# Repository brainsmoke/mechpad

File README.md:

# mechanical keypad

|  |
|-|
|  |

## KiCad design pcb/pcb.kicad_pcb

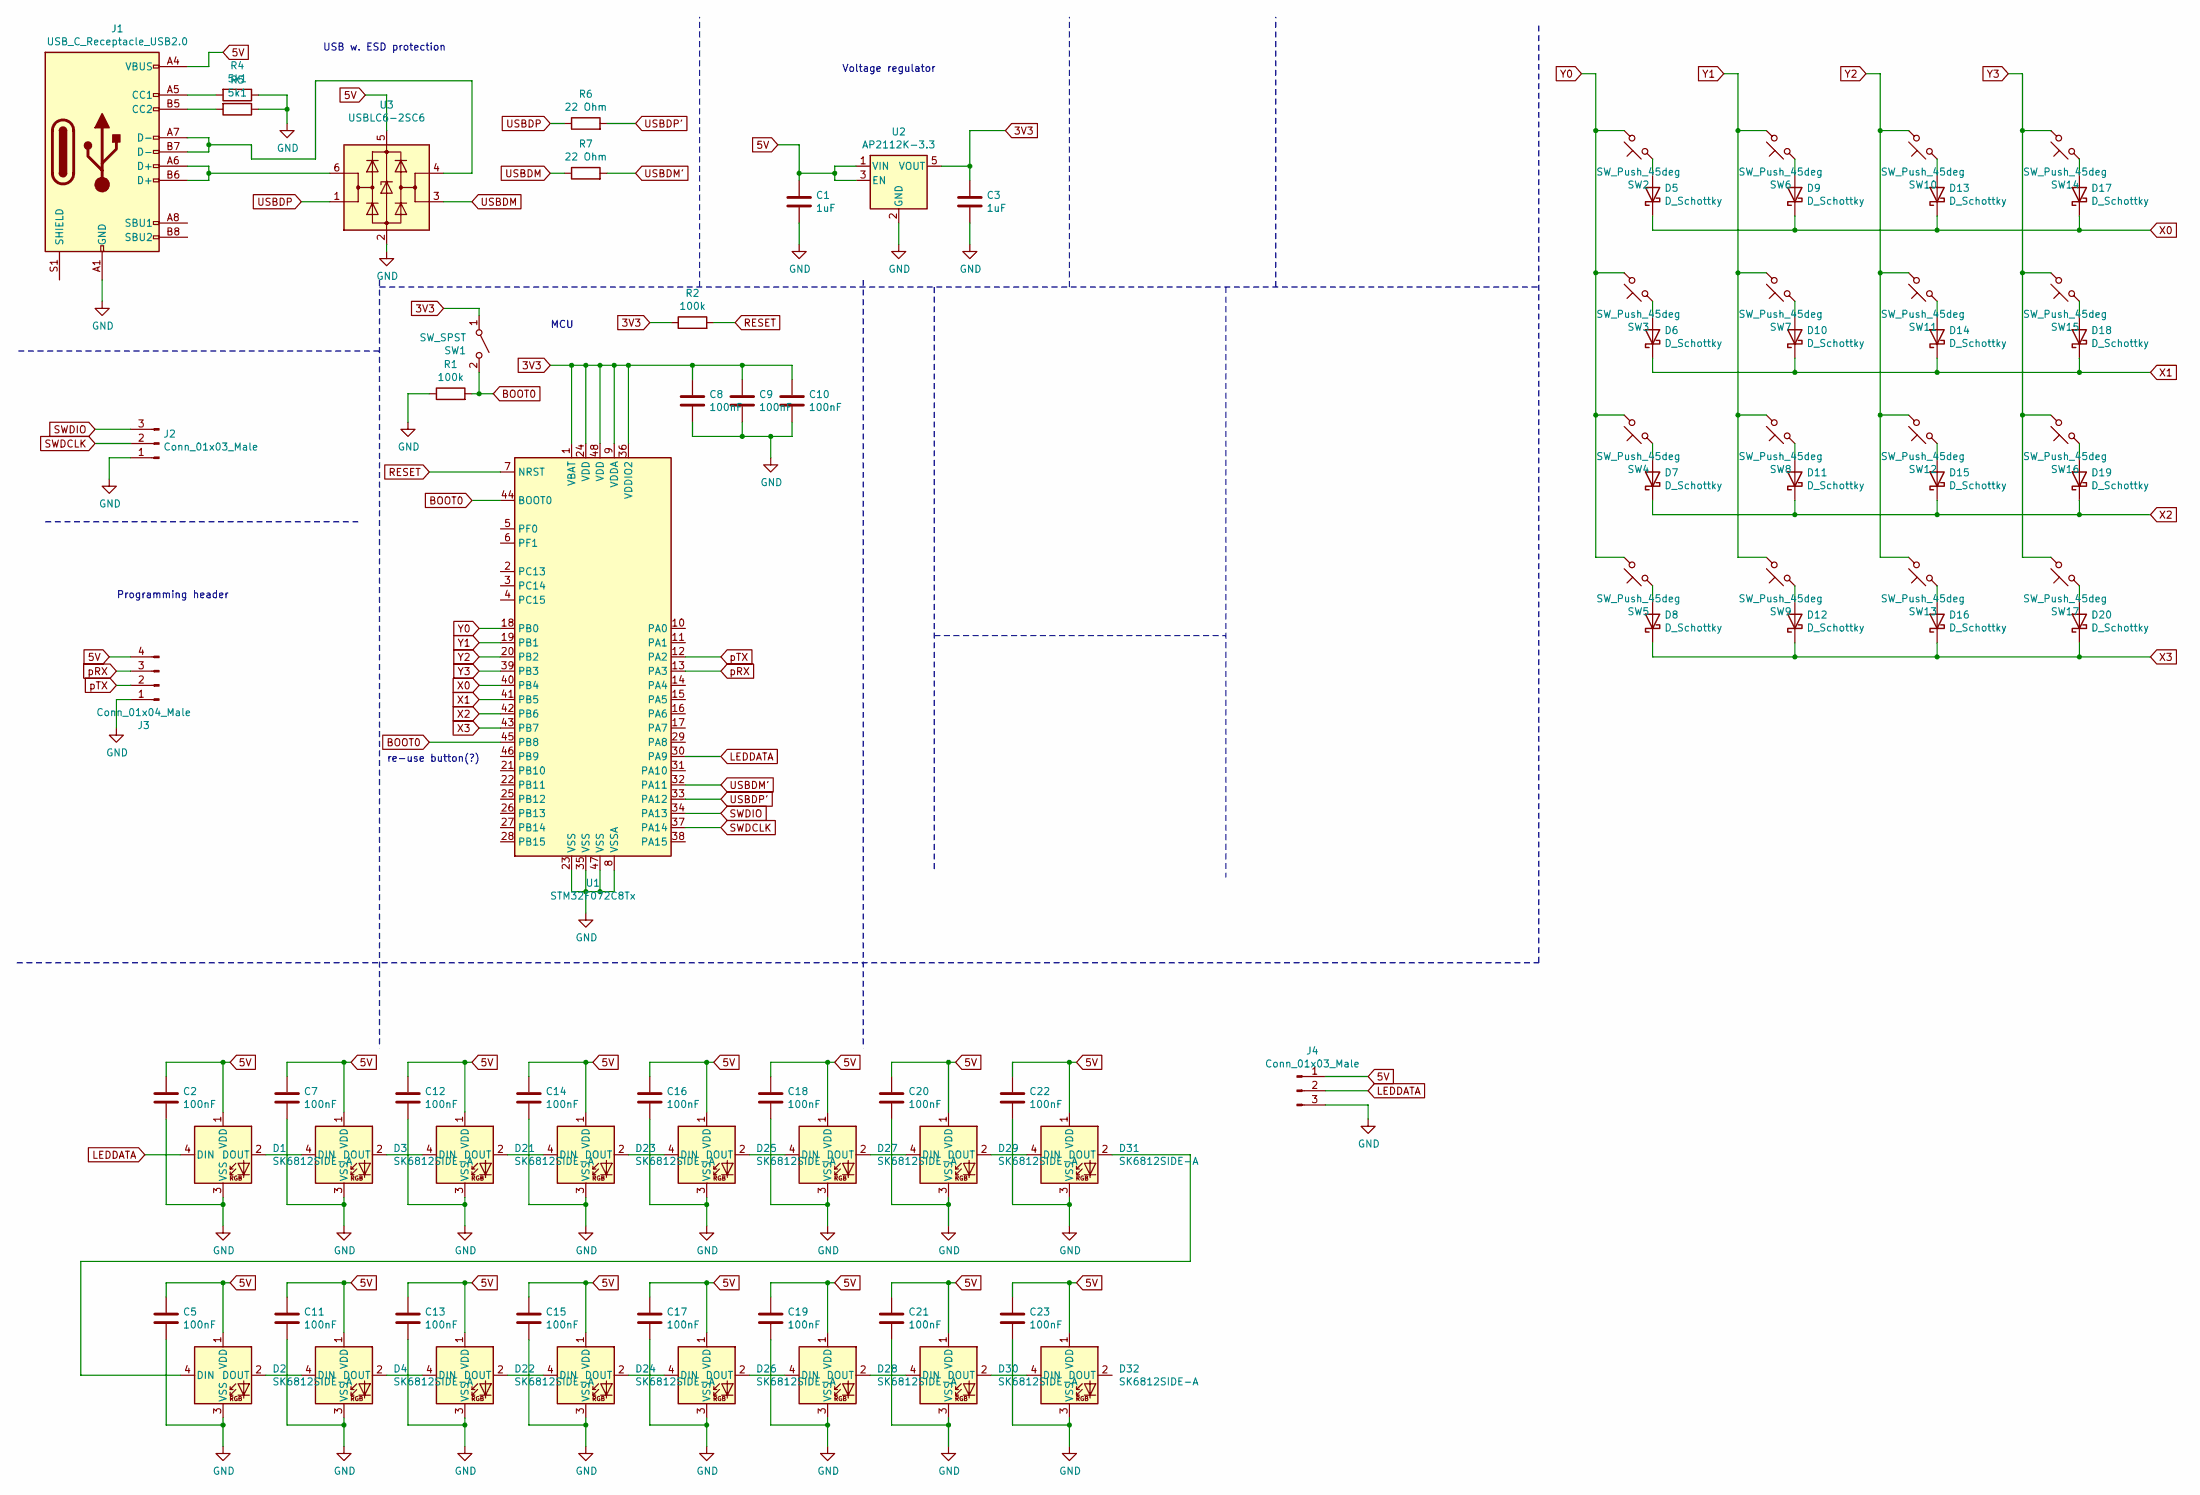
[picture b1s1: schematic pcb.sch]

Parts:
C1, C3: 1uF; C_0603_1608Metric
C2, C5, C7, C8, C9, C10, C11, C12, C13, C14, C15, C16, C17, C18, C19, C20, C21, C22, C23: 100nF; C_0603_1608Metric; LCSC C14663
D1, D2, D3, D4, D21, D22, D23, D24, D25, D26, D27, D28, D29, D30, D31, D32: SK6812SIDE-A; LED_SK6812SIDE-A_4020_pinlayout_asif50505-padssecure; LCSC C2890037
D5, D6, D7, D8, D9, D10, D11, D12, D13, D14, D15, D16, D17, D18, D19, D20: D_Schottky; D_SOD-123
J1: USB_C_Receptacle_USB2.0; USB_C_Receptacle_HRO_TYPE-C-31-M-12
J2, J4: Conn_01x03_Male; PinHeader_1x03_P2.54mm_Vertical
J3: Conn_01x04_Male; PinHeader_1x04_P2.54mm_Vertical
R1, R2: 100k; R_0603_1608Metric
R4, R5: 5k1; R_0603_1608Metric
R6, R7: 22 Ohm; R_0603_1608Metric
SW1: SW_SPST; SW_Push_1P1T_NO_CK_KMR2
SW2, SW3, SW4, SW5, SW6, SW7, SW8, SW9, SW10, SW11, SW12, SW13, SW14, SW15, SW16, SW17: SW_Push_45deg; SW_Cherry_MX_1.00u_PCB
U1: STM32F072C8Tx; LQFP-48_7x7mm_P0.5mm
U2: AP2112K-3.3; SOT-23-5
U3: USBLC6-2SC6; SOT-23-6

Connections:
3V3: C3.1, C8.1, C9.1, C10.1, R2.1, SW1.1 (A), U1.1 (VBAT), U1.9 (VDDA), U1.24 (VDD), U1.36 (VDDIO2), U1.48 (VDD), U2.5 (VOUT)
5V: C1.1, C2.1, C5.1, C7.1, C11.1, C12.1, C13.1, C14.1, C15.1, C16.1, C17.1, C18.1, C19.1, C20.1, C21.1, C22.1, C23.1, D1.1 (VDD), D2.1 (VDD), D3.1 (VDD), D4.1 (VDD), D21.1 (VDD), D22.1 (VDD), D23.1 (VDD), D24.1 (VDD), D25.1 (VDD), D26.1 (VDD), D27.1 (VDD), D28.1 (VDD), D29.1 (VDD), D30.1 (VDD), D31.1 (VDD), D32.1 (VDD), J1.A4 (VBUS), J1.A9 (VBUS), J1.B4 (VBUS), J1.B9 (VBUS), J3.4, J4.1, U2.1 (VIN), U2.3 (EN), U3.5 (VBUS)
BOOT0: R1.2, SW1.2 (B), U1.44 (BOOT0), U1.45 (PB8)
GND: C1.2, C2.2, C3.2, C5.2, C7.2, C8.2, C9.2, C10.2, C11.2, C12.2, C13.2, C14.2, C15.2, C16.2, C17.2, C18.2, C19.2, C20.2, C21.2, C22.2, C23.2, D1.3 (VSS), D2.3 (VSS), D3.3 (VSS), D4.3 (VSS), D21.3 (VSS), D22.3 (VSS), D23.3 (VSS), D24.3 (VSS), D25.3 (VSS), D26.3 (VSS), D27.3 (VSS), D28.3 (VSS), D29.3 (VSS), D30.3 (VSS), D31.3 (VSS), D32.3 (VSS), J1.A1 (GND), J1.A12 (GND), J1.B1 (GND), J1.B12 (GND), J2.1, J3.1, J4.3, R1.1, R4.1, R5.1, U1.8 (VSSA), U1.23 (VSS), U1.35 (VSS), U1.47 (VSS), U2.2 (GND), U3.2 (GND)
LEDDATA: D1.4 (DIN), J4.2, U1.30 (PA9)
unnamed: D1.2 (DOUT), D3.4 (DIN)
unnamed: D2.2 (DOUT), D4.4 (DIN)
unnamed: D2.4 (DIN), D31.2 (DOUT)
unnamed: D5.2 (A), SW2.1
unnamed: D6.2 (A), SW3.1
unnamed: D7.2 (A), SW4.1
unnamed: D8.2 (A), SW5.1
unnamed: D9.2 (A), SW6.1
unnamed: D10.2 (A), SW7.1
unnamed: D11.2 (A), SW8.1
unnamed: D12.2 (A), SW9.1
unnamed: D13.2 (A), SW10.1
unnamed: D14.2 (A), SW11.1
unnamed: D15.2 (A), SW12.1
unnamed: D16.2 (A), SW13.1
unnamed: D17.2 (A), SW14.1
unnamed: D18.2 (A), SW15.1
unnamed: D19.2 (A), SW16.1
unnamed: D20.2 (A), SW17.1
unnamed: D21.2 (DOUT), D23.4 (DIN)
unnamed: D3.2 (DOUT), D21.4 (DIN)
unnamed: D22.2 (DOUT), D24.4 (DIN)
unnamed: D4.2 (DOUT), D22.4 (DIN)
unnamed: D23.2 (DOUT), D25.4 (DIN)
unnamed: D24.2 (DOUT), D26.4 (DIN)
unnamed: D25.2 (DOUT), D27.4 (DIN)
unnamed: D26.2 (DOUT), D28.4 (DIN)
unnamed: D27.2 (DOUT), D29.4 (DIN)
unnamed: D28.2 (DOUT), D30.4 (DIN)
unnamed: D29.2 (DOUT), D31.4 (DIN)
unnamed: D30.2 (DOUT), D32.4 (DIN)
unnamed: J1.A5 (CC1), R4.2
unnamed: J1.A6 (D+), J1.B6 (D+), U3.6 (I/O1)
unnamed: J1.A7 (D-), J1.B7 (D-), U3.4 (I/O2)
unnamed: J1.B5 (CC2), R5.2
RESET: R2.2, U1.7 (NRST)
SWDCLK: J2.2, U1.37 (PA14)
SWDIO: J2.3, U1.34 (PA13)
USBDM: R7.1, U3.3 (I/O2)
USBDM': R7.2, U1.32 (PA11)
USBDP: R6.1, U3.1 (I/O1)
USBDP': R6.2, U1.33 (PA12)
X0: D5.1 (K), D9.1 (K), D13.1 (K), D17.1 (K), U1.40 (PB4)
X1: D6.1 (K), D10.1 (K), D14.1 (K), D18.1 (K), U1.41 (PB5)
X2: D7.1 (K), D11.1 (K), D15.1 (K), D19.1 (K), U1.42 (PB6)
X3: D8.1 (K), D12.1 (K), D16.1 (K), D20.1 (K), U1.43 (PB7)
Y0: SW2.2, SW3.2, SW4.2, SW5.2, U1.18 (PB0)
Y1: SW6.2, SW7.2, SW8.2, SW9.2, U1.19 (PB1)
Y2: SW10.2, SW11.2, SW12.2, SW13.2, U1.20 (PB2)
Y3: SW14.2, SW15.2, SW16.2, SW17.2, U1.39 (PB3)
pRX: J3.3, U1.13 (PA3)
pTX: J3.2, U1.12 (PA2)

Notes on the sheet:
Programming header
USB w. ESD protection
Voltage regulator
MCU
re-use button(?)

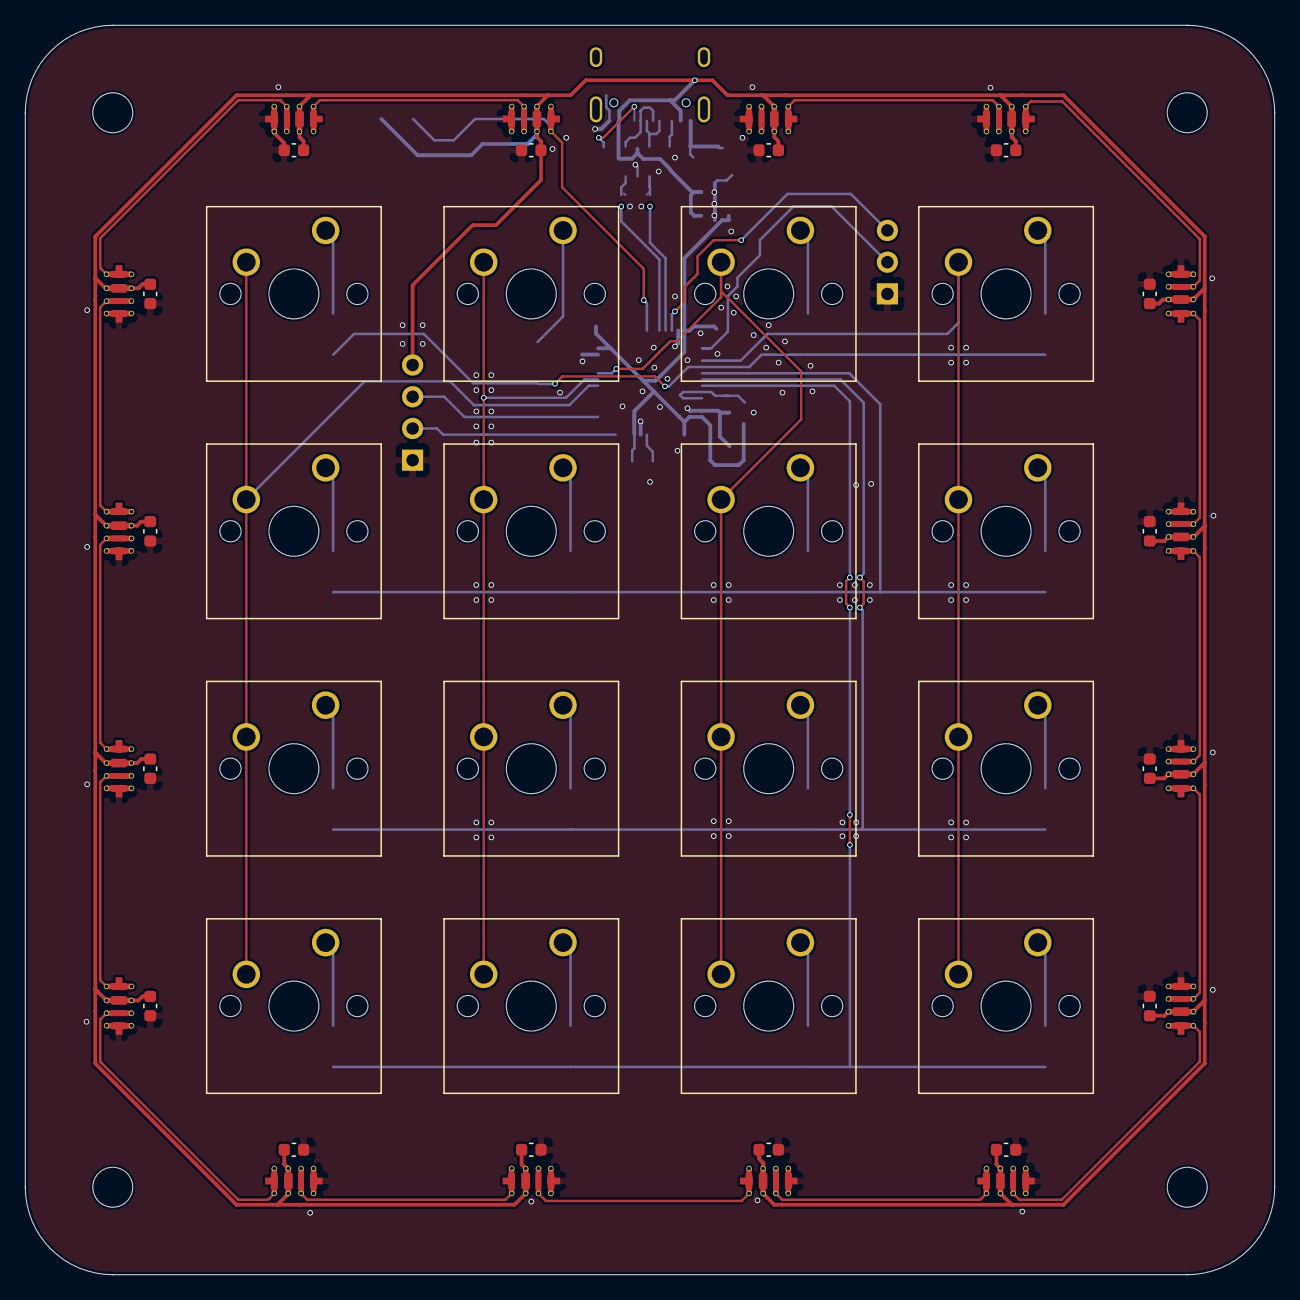
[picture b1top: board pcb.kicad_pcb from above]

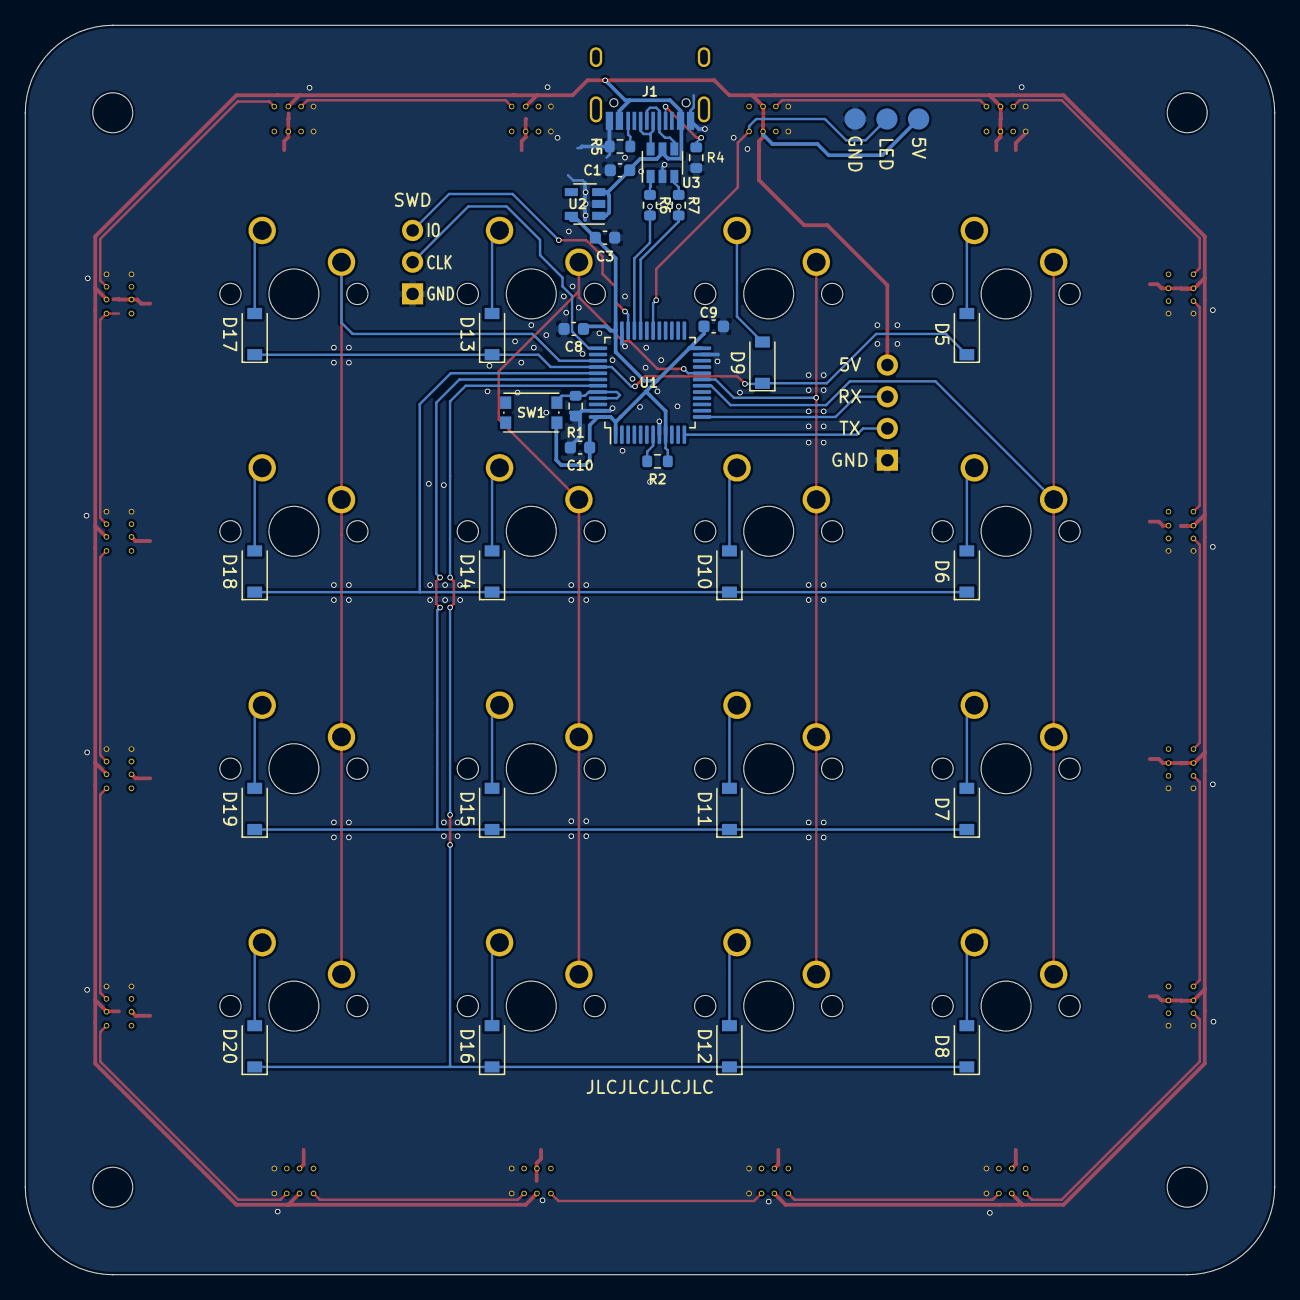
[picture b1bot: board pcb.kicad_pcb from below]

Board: 2 copper layers, 100.0 x 100.0 mm, 83 parts (34 on the bottom side), 57 nets.

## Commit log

2023-10-17 init commit
2023-10-17 change headers
2023-10-17 add gerbers
2023-10-17 move pcb to subdir
2023-10-20 add keycap files
2023-10-21 rename dir
2023-10-21 add empty glyph
2023-10-21 clean up construction in flat_keys.scad
2023-10-21 add stl files
2023-11-01 correct silkscreen labels (oops)
2023-11-02 make leds work
2023-11-03 mak keys work
2023-11-03 move led code to common dir
2023-11-03 add some more led animations
2023-11-03 add boot0 button
2023-11-03 remove osc.
2023-11-03 compensate for weak red
2023-11-03 factor out keypad code
2023-11-04 stm32f103 -> stm32f072
2023-11-04 remove obsolete comment
2023-11-04 add ELF to DeFUse tool
2023-11-04 the big endian in the spec is a lie (at least in dfu-util
2023-11-11 make leds brighter
2023-11-11 add images
2023-11-12 add case
2023-11-18 add USB HID keypad example
2023-11-18 add link to HID key definitions document
2023-11-18 fix name of consumer page
2023-11-18 change key bindings
2023-11-19 improve animation
2023-11-19 remove ferrite
2023-11-19 wait for descriptor read before sending packets
2023-11-19 use common code for animations
2023-11-19 add led probe pads
2023-11-21 make solder pads more solid in case of desoldering
2023-11-22 optimize tracks
2023-11-23 speed up animation
2023-11-24 add usb serial example
2023-11-24 mpd frontend
2023-11-27 ws2812b-4020 -> sk6812-side-a
2023-11-28 don't block when the OS isn't listening
2023-11-28 increase clearance
2023-11-28 add comment with possible tweaks
2023-12-15 add case for v2
2023-12-15 add gerbers for v2
2023-12-17 remove unecessary pull-up on USB-DP
2024-04-10 case for v2 improvements
2024-06-29 add key STLs optimised for fdm
2024-07-05 use Makefile for keys
2024-07-26 add pcb cache
